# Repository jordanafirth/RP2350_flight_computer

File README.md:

# Undergraduate flight computer

Custom Feather-size data logger for a reusable teaching fleet: 2,000 initial units and approximately 200 replacement units per year.

- [Development plan](docs/development-plan.md)
- [Requirements and open decisions](docs/requirements.md)
- [Architecture](docs/architecture.md)
- [Candidate GPIO allocation](docs/pin-allocation.md)
- [Reference findings](docs/reference-findings.md)
- [Part selections](docs/parts-selection.md)
- [Schematic draft and review notes](docs/schematic-review.md)
- [Placement and mechanical review](docs/placement-review.md)
- [Routing development review](docs/routing-review.md)
- [Reference acquisition](references/README.md)

Status: four-layer routing is complete, with all signal and ground nets connected. Native checks report zero unconnected items and no copper violations; only the two reviewed USB locating-hole notices remain. USB and underside microSD share one short end; four right-angle servo ports are at the other. Fabricator impedance confirmation, physical prototype validation and a PCBA quote remain open. There is no manufacturing release.

The current product is an RP2040 Feather Adalogger connected by Qwiic cables to BMP280 and BNO085 breakouts, powered by a small single-cell lithium-ion battery. The target combines these functions, preferably using RP2350, and adds factory-installed servo and power-control connectors.

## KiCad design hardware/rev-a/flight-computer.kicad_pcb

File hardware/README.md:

# Hardware work in progress

`imports/` contains local, ignored intermediate vendor conversions, not the custom board. In particular, the reference RP2350 Feather includes an HSTX display connector that is explicitly excluded from the custom design. The rebuild script regenerates its required board conversions from pinned sources.

`rev-a/flight-computer.kicad_pro` is the integrated custom schematic project, with a local symbol library and footprint library. It is a development draft and must not be sent for manufacturing.

`rev-a/flight-computer.kicad_pcb` contains the completed four-layer routing candidate. USB and underside microSD occupy the same short end; four right-angle servo ports occupy the opposite end. The retained Qwiic connector is horizontal. The battery socket remains on top in the reference Feather location. Reports in `reports/pcb/` are named development checkpoints, with historical intermediate results retained; current results are in `current-drc.json` and `routing-completion.json`. Mechanical review and remaining release gates are in `docs/placement-review.md`.

Upstream Adafruit-derived circuits retain the attribution and CC BY-SA 3.0 notices in `references/`. Changes include integration, connector changes, GPIO reassignment and removal of breakout-only interfaces. No Adafruit endorsement is implied.

## Rebuilding

After reference acquisition, run `tools/rebuild-hardware.ps1`. It uses an existing KiCad CLI and Python interpreter; optional `-KiCadCli` and `-Python` parameters override discovery. Schematic generation and checks use the Python standard library. Placement, metadata synchronization and routing interchange require KiCad's bundled Python with `pcbnew` and `wx`; they initialize KiCad's native project API without opening the editor.

Generation overwrites the custom draft from the model in `tools/build-draft-schematic.py`. If editing the native CAD manually, first preserve the edits and reconcile them into the generator before running it again.

Run `tools/place-pcb.py` after rebuilding the schematic and footprints to regenerate the placement; this also overwrites the PCB. It uses the local KiCad footprint libraries in addition to the converted project library. Do not run it over a manually routed board without preserving and reconciling those changes.

See [review notes](../docs/schematic-review.md) and [hardware attribution](NOTICE.md).

## Checking and routing

`tools/check-hardware.ps1` runs the current schematic and PCB checks without regenerating the PCB. Its `-PreviewOnly` option renders cropped top/bottom engineering views. Always inspect the raw DRC results; successful report generation does not mean a clean board.

`tools/route-board.py` provides native KiCad DSN/SES interchange. Use KiCad's bundled Python. Exporting with `--fresh-routing` omits existing tracks from the routing input; importing with `--replace-tracks` replaces candidate tracks and requires a prior backup. The completed four-layer board uses both inner layers for signals and ground fill, retaining local USB/clock reference reservations. Older three-signal-layer experiments do not describe the current stackup.

`tools/run-router.ps1` runs the locally verified Freerouting 2.0.1 library through `tools/RouteBoard.java`, with an explicit pass limit and synchronous SES export. The upstream 2.0.1 CLI scheduler did not honor the requested routing stop and could race SES serialization; do not use its normal CLI entry point for this project. The wrapper starts no GUI, API server or analytics. Routing output still requires independent KiCad checks and engineering review.

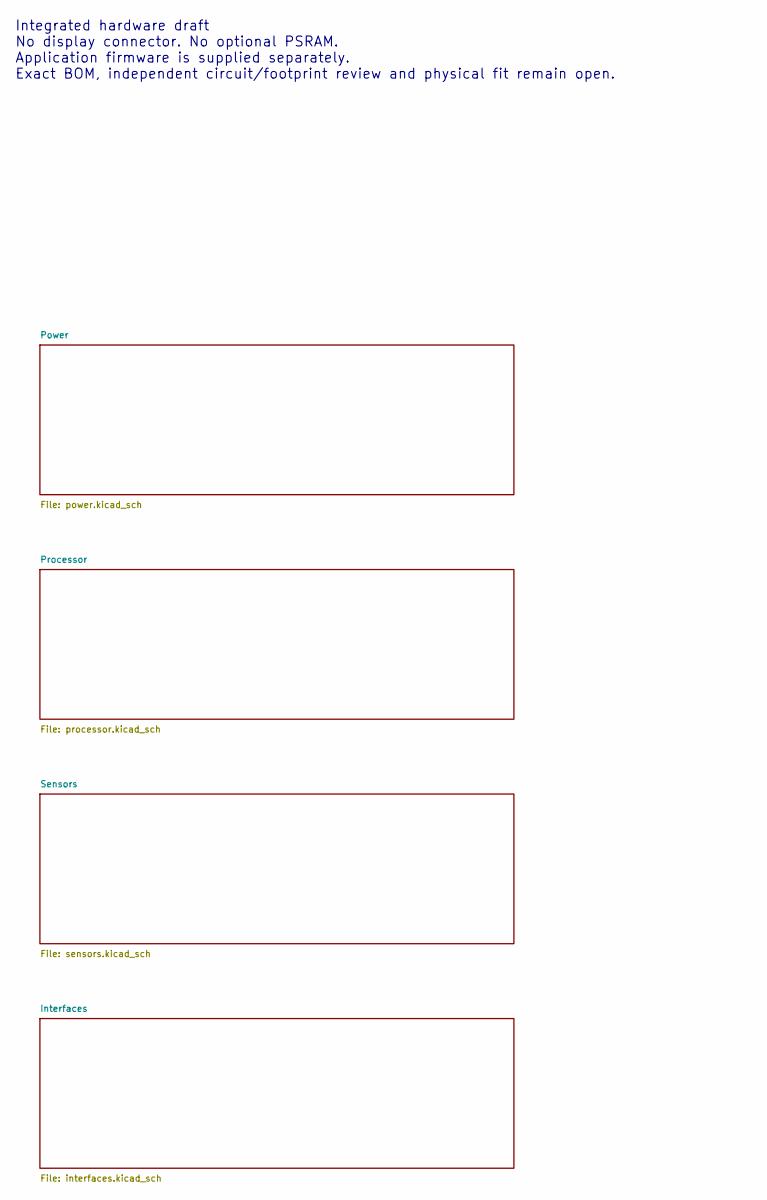
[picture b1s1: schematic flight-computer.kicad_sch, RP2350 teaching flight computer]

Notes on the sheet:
Integrated hardware draft No display connector. No optional PSRAM. Application firmware is supplied separately. Exact BOM, independent circuit/footprint review and physical fit remain open.

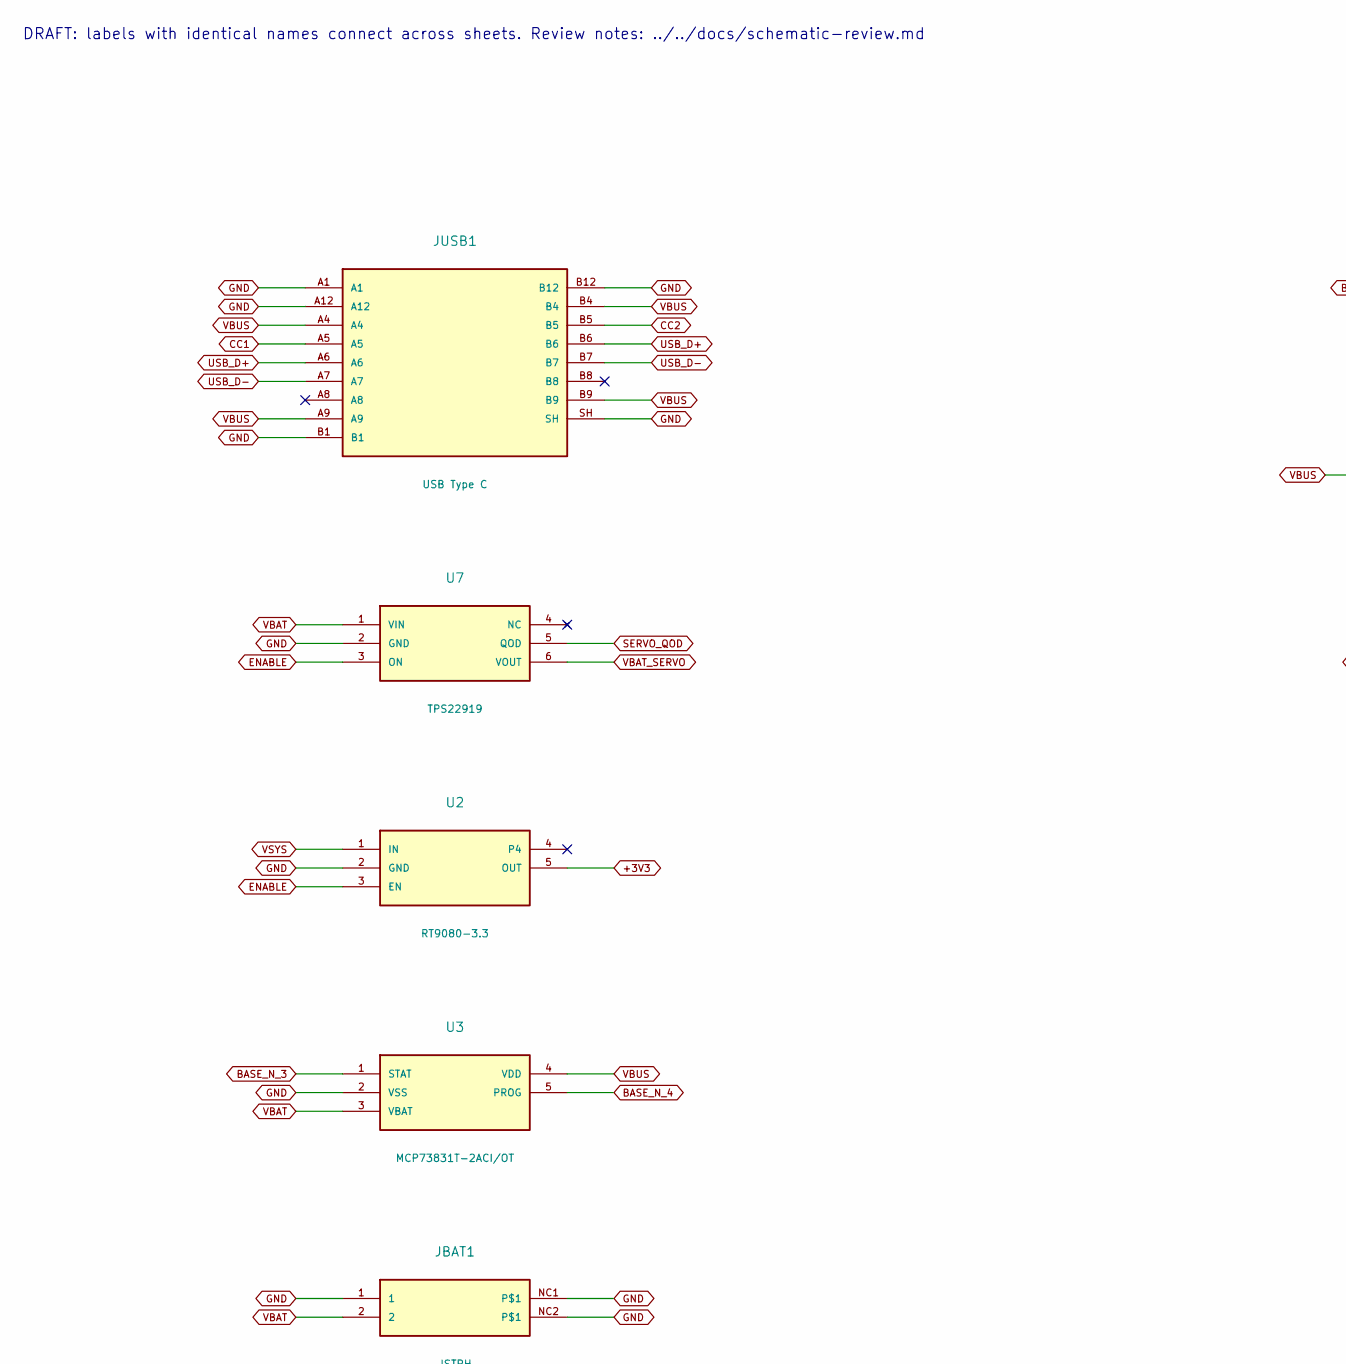
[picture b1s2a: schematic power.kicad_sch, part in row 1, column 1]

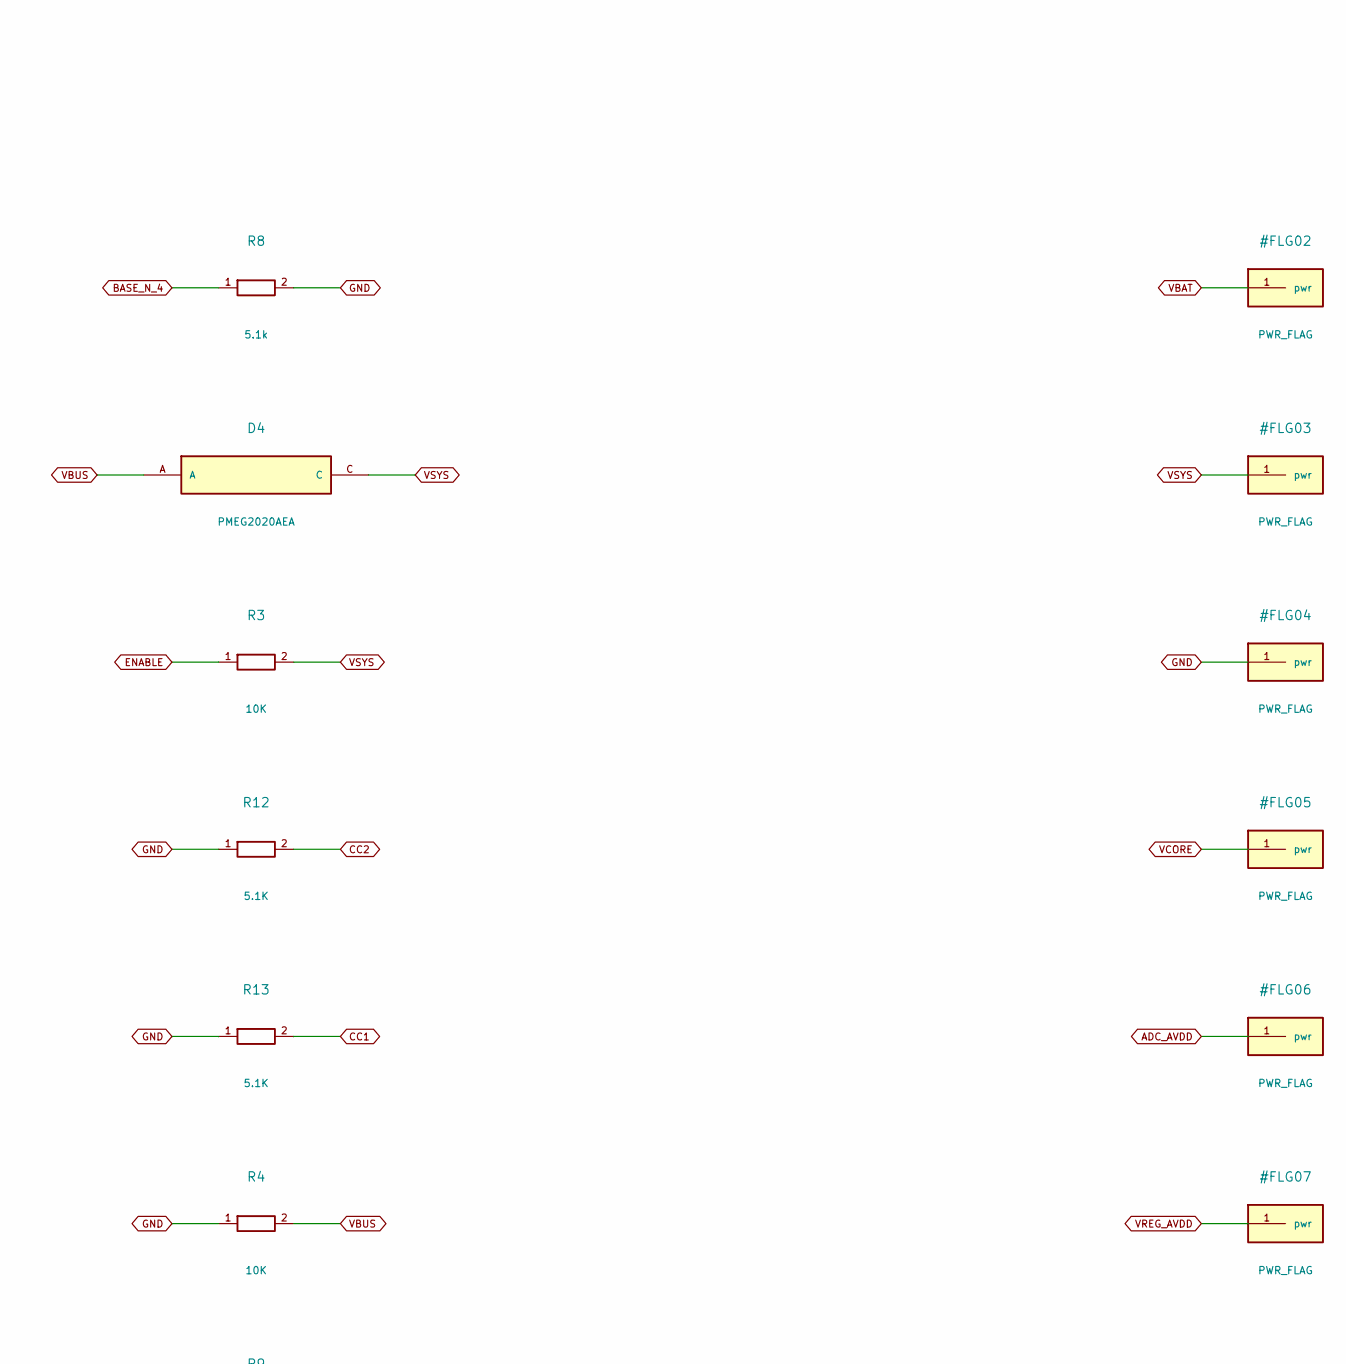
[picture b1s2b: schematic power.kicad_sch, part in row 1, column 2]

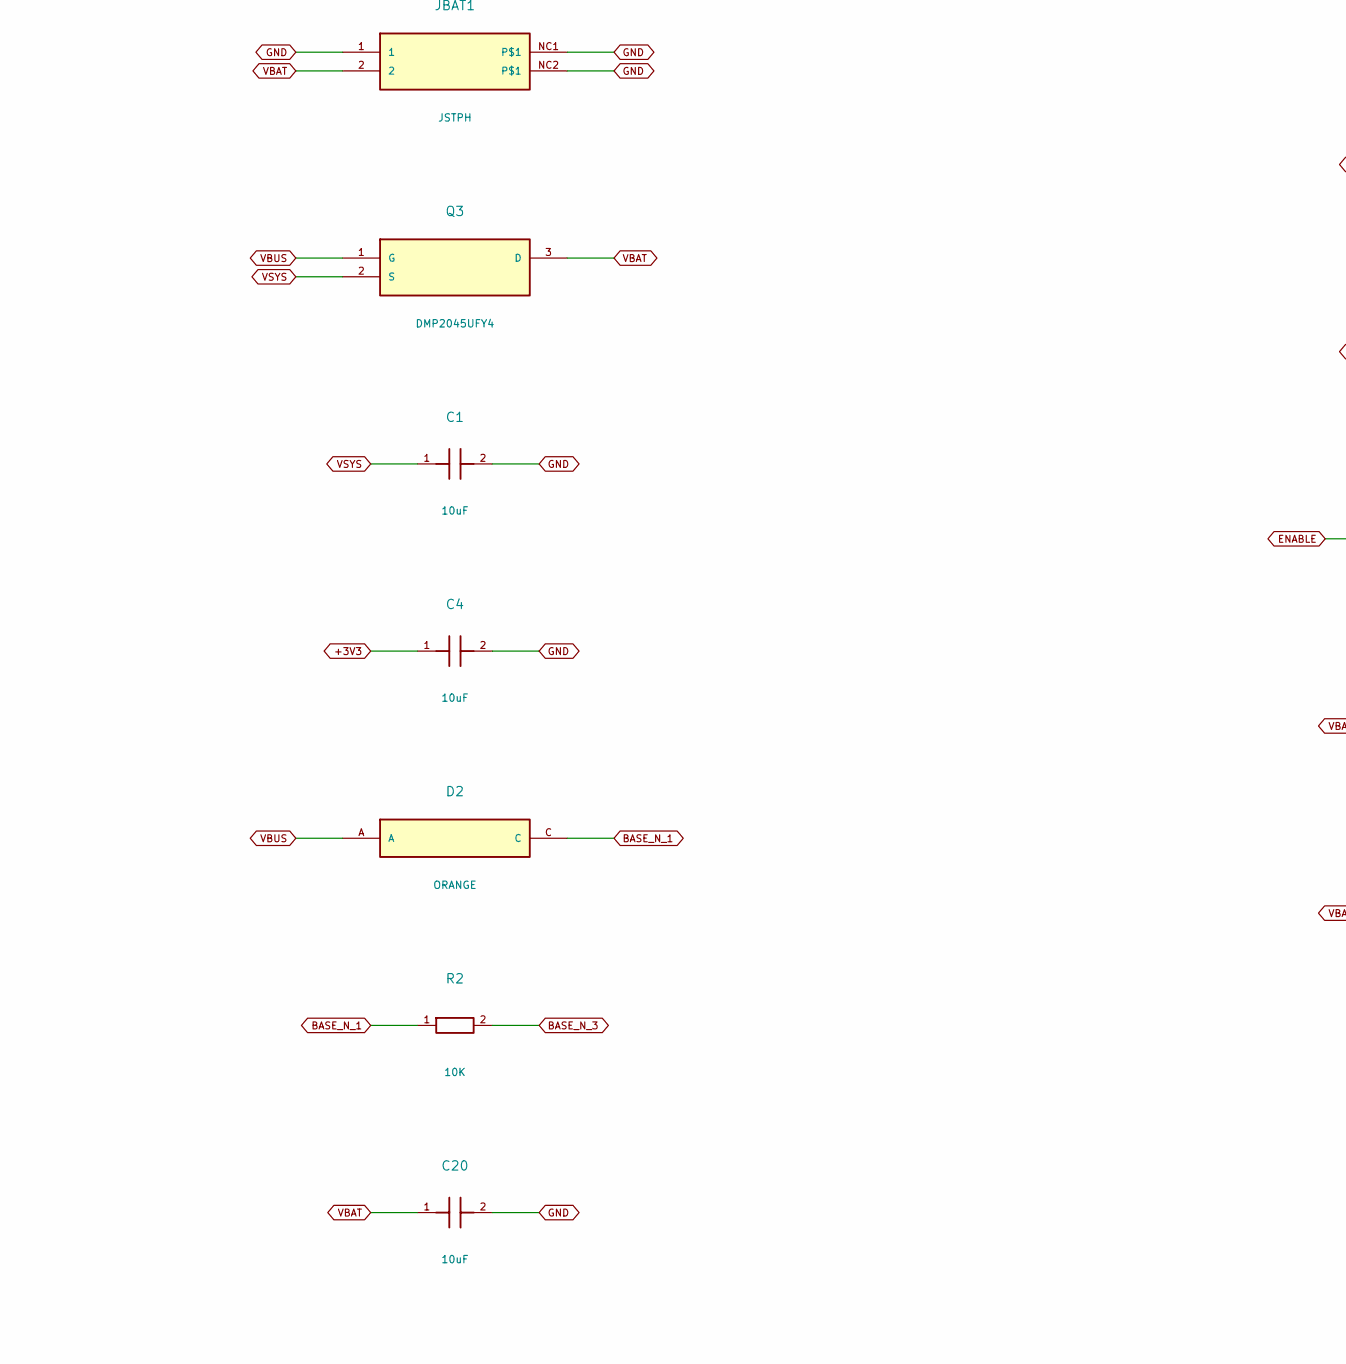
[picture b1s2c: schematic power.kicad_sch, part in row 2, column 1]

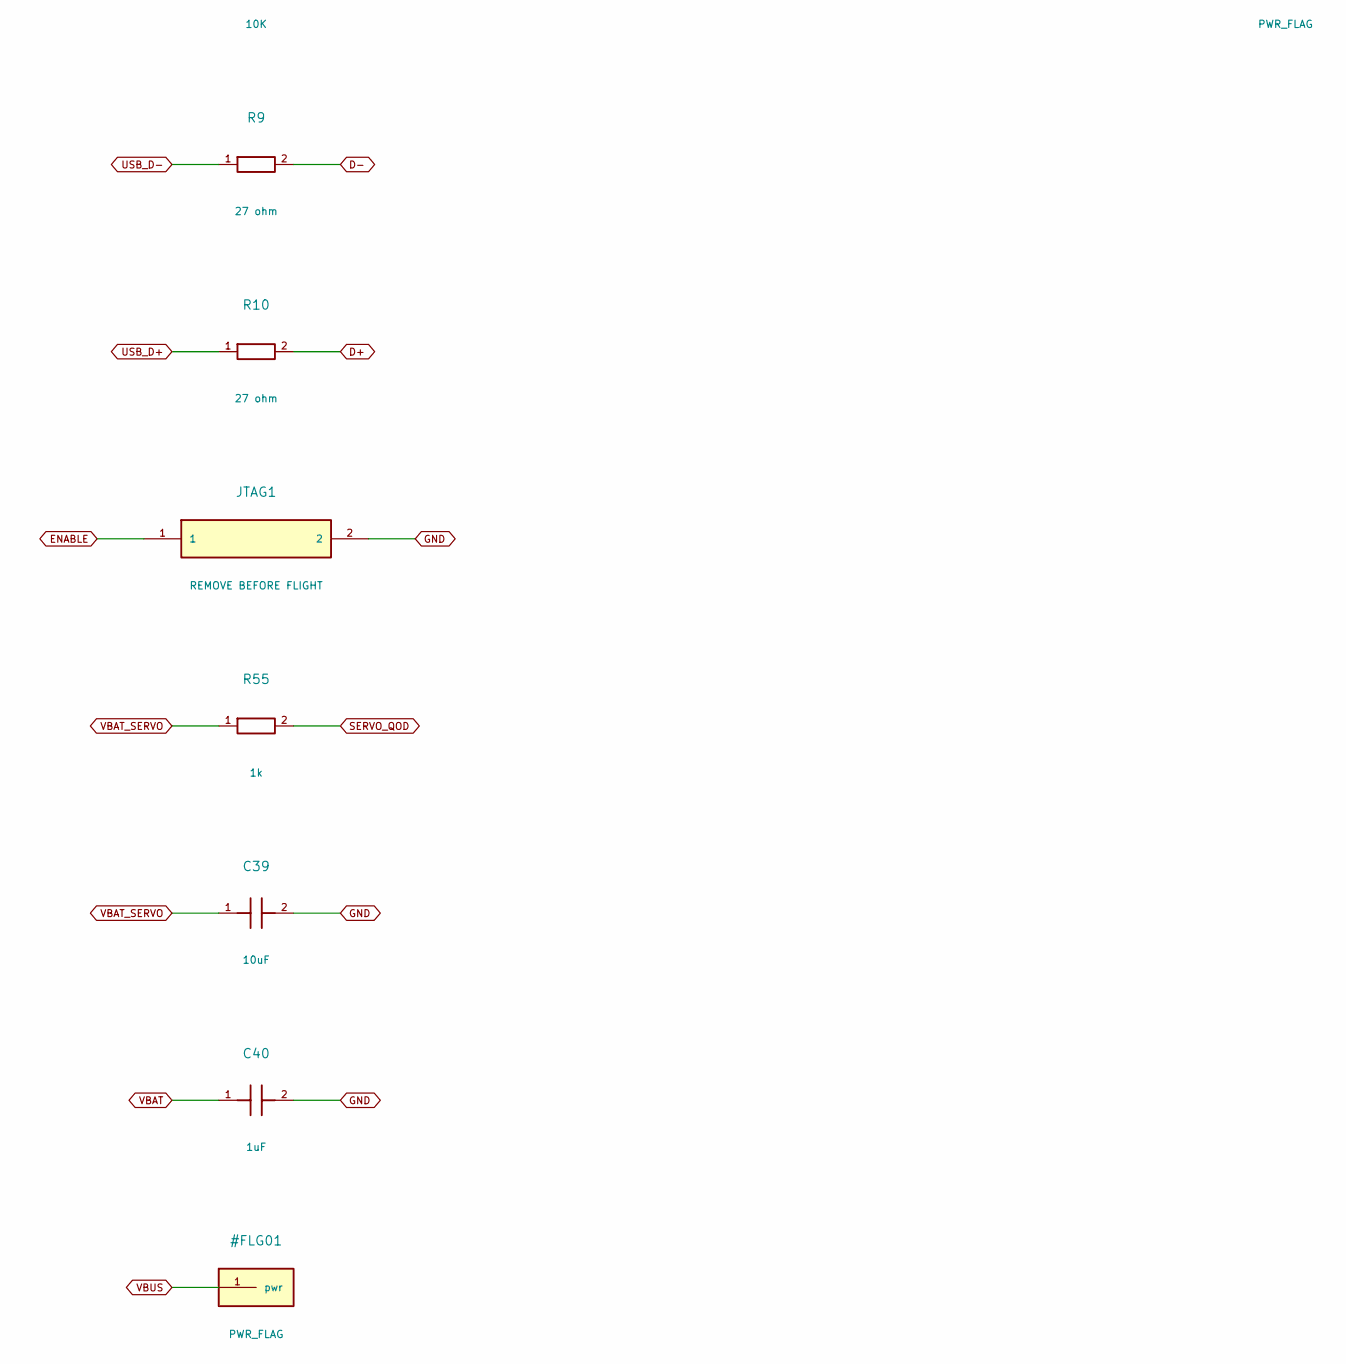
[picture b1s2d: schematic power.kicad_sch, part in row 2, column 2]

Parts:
C1, C4, C20: 10uF; 0805-NO; MPN GRM21BR61A106KE19L
C39: 10uF; C_0805_2012Metric; MPN GRM21BR61A106KE19L
C40: 1uF; C_0603_1608Metric; MPN GRM188R61A105KA61D
D2: ORANGE; CHIPLED_0603_NOOUTLINE; MPN LTST-C190KFKT
D4: PMEG2020AEA; SOD-323F; MPN PMEG2020AEA,115
JBAT1: JSTPH; JSTPH2_BATT; MPN S2B-PH-SM4-TB(LF)(SN)
JTAG1: REMOVE BEFORE FLIGHT; JST_SH_BM02B-SRSS-TB_1x02-1MP_P1.00mm_Vertical; MPN BM02B-SRSS-TB(LF)(SN)
JUSB1: USB Type C; USB_C_Receptacle_GCT_USB4110; MPN USB4110-GF-A
Q3: DMP2045UFY4; DFN2015-3; MPN DMP2045UFY4-7
R2, R3, R4: 10K; _0402NO; MPN RC0402FR-0710KL
R8: 5.1k; _0402NO; MPN RC0402FR-075K1L
R9, R10: 27 ohm; _0402NO; MPN RC0402FR-0727RL
R12, R13: 5.1K; _0402NO; MPN RC0402FR-075K1L
R55: 1k; R_0603_1608Metric; MPN RC0603FR-071KL
U2: RT9080-3.3; SOT23-5; MPN RT9080-33GJ5
U3: MCP73831T-2ACI/OT; SOT23-5; MPN MCP73831T-2ACI/OT
U7: TPS22919; SOT-363_SC-70-6; MPN TPS22919DCKR

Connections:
+3V3: C4.1, U2.5 (OUT); also elsewhere on the board
BASE_N_1: D2.C, R2.1
BASE_N_3: R2.2, U3.1 (STAT)
BASE_N_4: R8.1, U3.5 (PROG)
CC1: JUSB1.A5, R13.2
CC2: JUSB1.B5, R12.2
D+: R10.2; also elsewhere on the board
D-: R9.2; also elsewhere on the board
ENABLE: JTAG1.1, R3.1, U2.3 (EN), U7.3 (ON); also elsewhere on the board
GND: C1.2, C4.2, C20.2, C39.2, C40.2, JBAT1.1, JBAT1.NC1, JBAT1.NC2, JTAG1.2, JUSB1.A1, JUSB1.A12, JUSB1.B1, JUSB1.B12, JUSB1.SH, R4.1, R8.2, R12.1, R13.1, U2.2 (GND), U3.2 (VSS), U7.2 (GND); also elsewhere on the board
SERVO_QOD: R55.2, U7.5 (QOD)
USB_D+: JUSB1.A6, JUSB1.B6, R10.1
USB_D-: JUSB1.A7, JUSB1.B7, R9.1
VBAT: C20.1, C40.1, JBAT1.2, Q3.3 (D), U3.3 (VBAT), U7.1 (VIN); also elsewhere on the board
VBAT_SERVO: C39.1, R55.1, U7.6 (VOUT); also elsewhere on the board
VBUS: D2.A, D4.A, JUSB1.A4, JUSB1.A9, JUSB1.B4, JUSB1.B9, Q3.1 (G), R4.2, U3.4 (VDD); also elsewhere on the board
VSYS: C1.1, D4.C, Q3.2 (S), R3.2, U2.1 (IN)

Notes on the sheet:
DRAFT: labels with identical names connect across sheets. Review notes: ../../docs/schematic-review.md

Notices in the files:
hardware/rev-a/flight-computer.kicad_sch:
Adafruit-derived circuits; CC BY-SA 3.0; see references and hardware/README.md
